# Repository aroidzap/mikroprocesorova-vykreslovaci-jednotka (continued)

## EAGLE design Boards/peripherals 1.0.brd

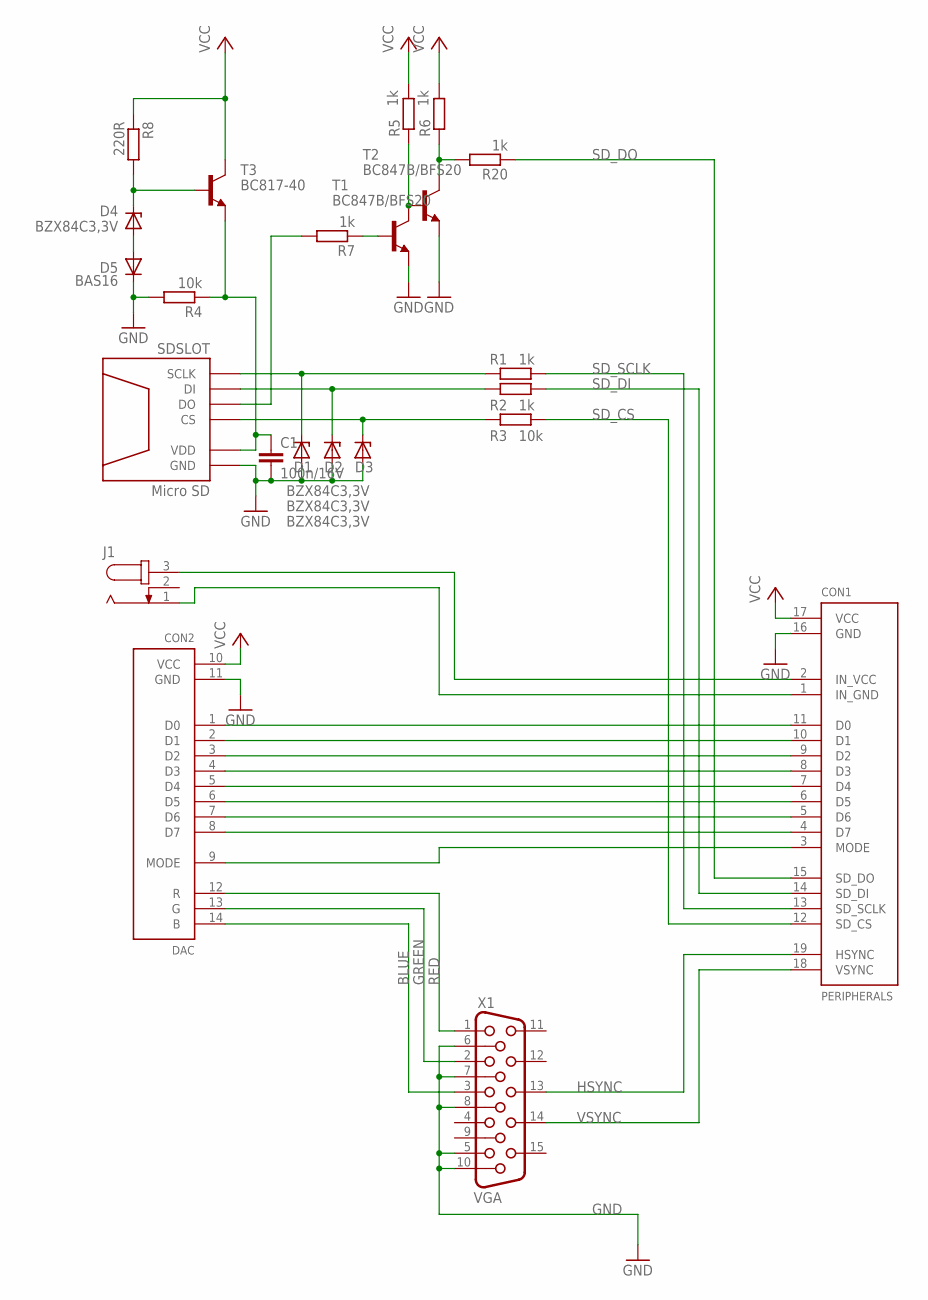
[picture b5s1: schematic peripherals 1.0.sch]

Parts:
C1: 100n/16V; C0603
CON1: PERIPHERALS; PERIPHERALS_CON
CON2: DAC; DAC_CON
D1, D2, D3, D4: BZX84C3,3V; SOT23
D5: BAS16; SOT23
J1: JACK-PLUG1; SPC4078
R1, R2, R5, R6, R7, R20: 1k; 0204/7
R3, R4: 10k; 0204/7
R8: 220R; R0603
SDSLOT: Micro SD; MICRO_SD_ATTEND
T1, T2: BC847B/BFS20; SOT23-BEC
T3: BC817-40; SOT23-BEC
X1: VGA; HDF15H

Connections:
BLUE: CON2.14 (B), X1.3
GND: C1.2, CON1.16 (GND), CON2.11 (GND), D1.1 (A), D2.1 (A), D3.1 (A), D5.3 (C), R4.2, SDSLOT.6 (GND), SDSLOT.CASE1 (GND), SDSLOT.CASE2 (GND), SDSLOT.CASE3 (GND), SDSLOT.CASE4 (GND), T1.E, T2.E, X1.5, X1.6, X1.7, X1.8, X1.10
GREEN: CON2.13 (G), X1.2
HSYNC: CON1.19 (HSYNC), X1.13
IN_GND: CON1.1 (IN_GND), J1.1
IN_VCC: CON1.2 (IN_VCC), J1.3
unnamed: D1.3 (C), R1.1, SDSLOT.5 (SCLK)
unnamed: D2.3 (C), R2.1, SDSLOT.3 (DI)
unnamed: D3.3 (C), R3.1, SDSLOT.2 (CS)
unnamed: D4.1 (A), D5.1 (A)
unnamed: C1.1, R4.1, SDSLOT.4 (VDD), T3.E
unnamed: D4.3 (C), R8.2, T3.B
unnamed: R6.1, R20.2, T2.C
unnamed: R7.2, SDSLOT.7 (DO)
unnamed: R5.1, T1.C, T2.B
unnamed: R7.1, T1.B
unnamed: CON1.11 (D0), CON2.1 (D0)
unnamed: CON1.10 (D1), CON2.2 (D1)
unnamed: CON1.9 (D2), CON2.3 (D2)
unnamed: CON1.8 (D3), CON2.4 (D3)
unnamed: CON1.7 (D4), CON2.5 (D4)
unnamed: CON1.6 (D5), CON2.6 (D5)
unnamed: CON1.5 (D6), CON2.7 (D6)
unnamed: CON1.4 (D7), CON2.8 (D7)
unnamed: CON1.3 (MODE), CON2.9 (MODE)
RED: CON2.12 (R), X1.1
SD_CS: CON1.12 (SD_CS), R3.2
SD_DI: CON1.14 (SD_DI), R2.2
SD_DO: CON1.15 (SD_DO), R20.1
SD_SCLK: CON1.13 (SD_SCLK), R1.2
VCC: CON1.17 (VCC), CON2.10 (VCC), R5.2, R6.2, R8.1, T3.C
VSYNC: CON1.18 (VSYNC), X1.14

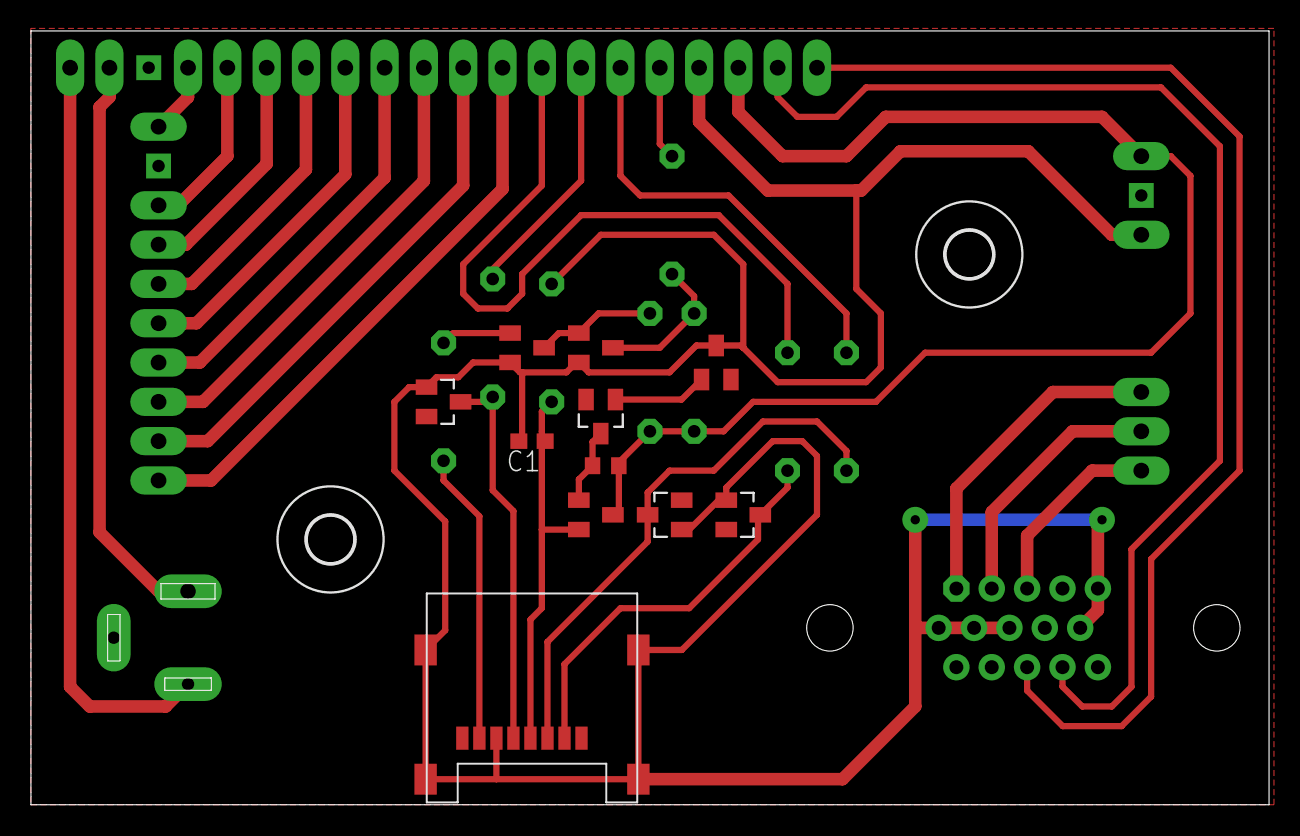
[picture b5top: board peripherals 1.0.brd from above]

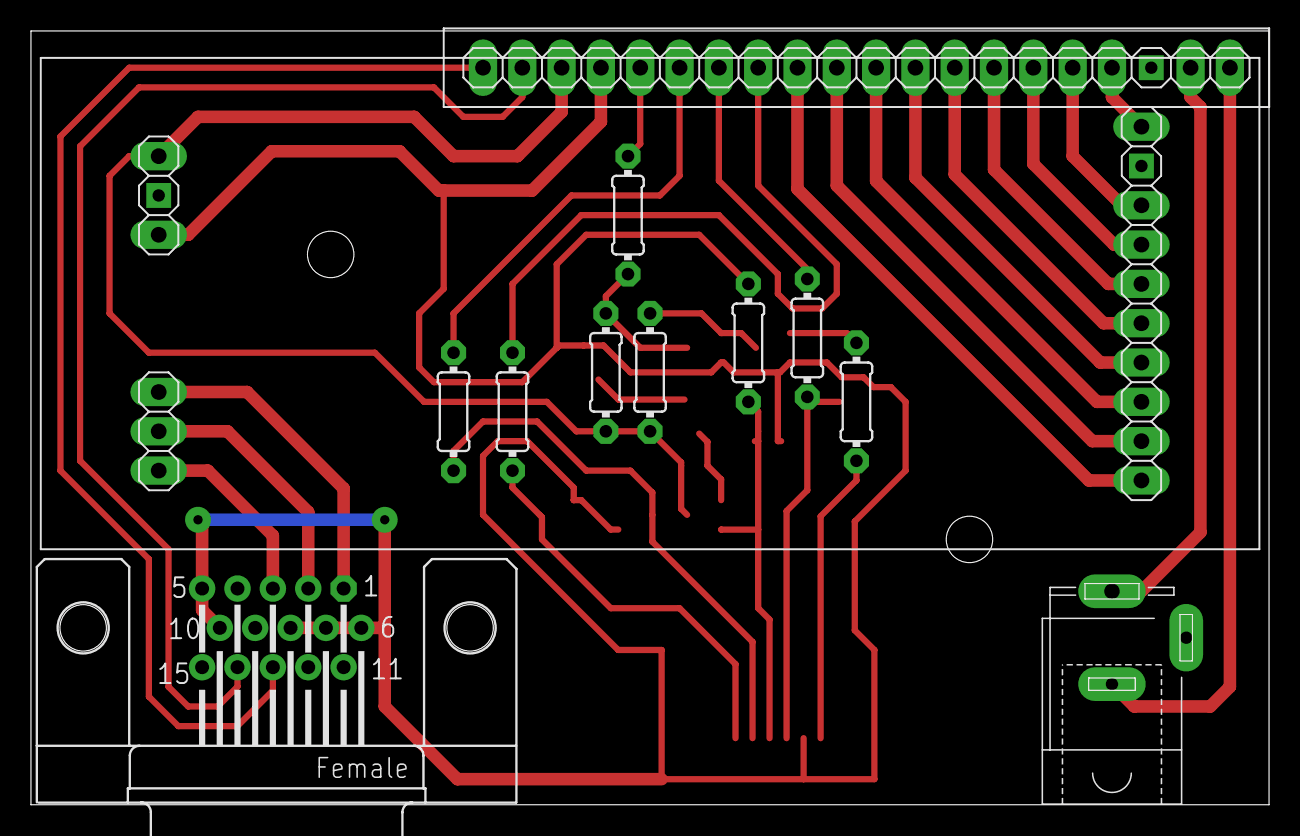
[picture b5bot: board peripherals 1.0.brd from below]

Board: 2 copper layers, 80.0 x 50.0 mm, 25 parts (12 on the bottom side), 32 nets.

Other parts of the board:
U$1, U$2: 3,0

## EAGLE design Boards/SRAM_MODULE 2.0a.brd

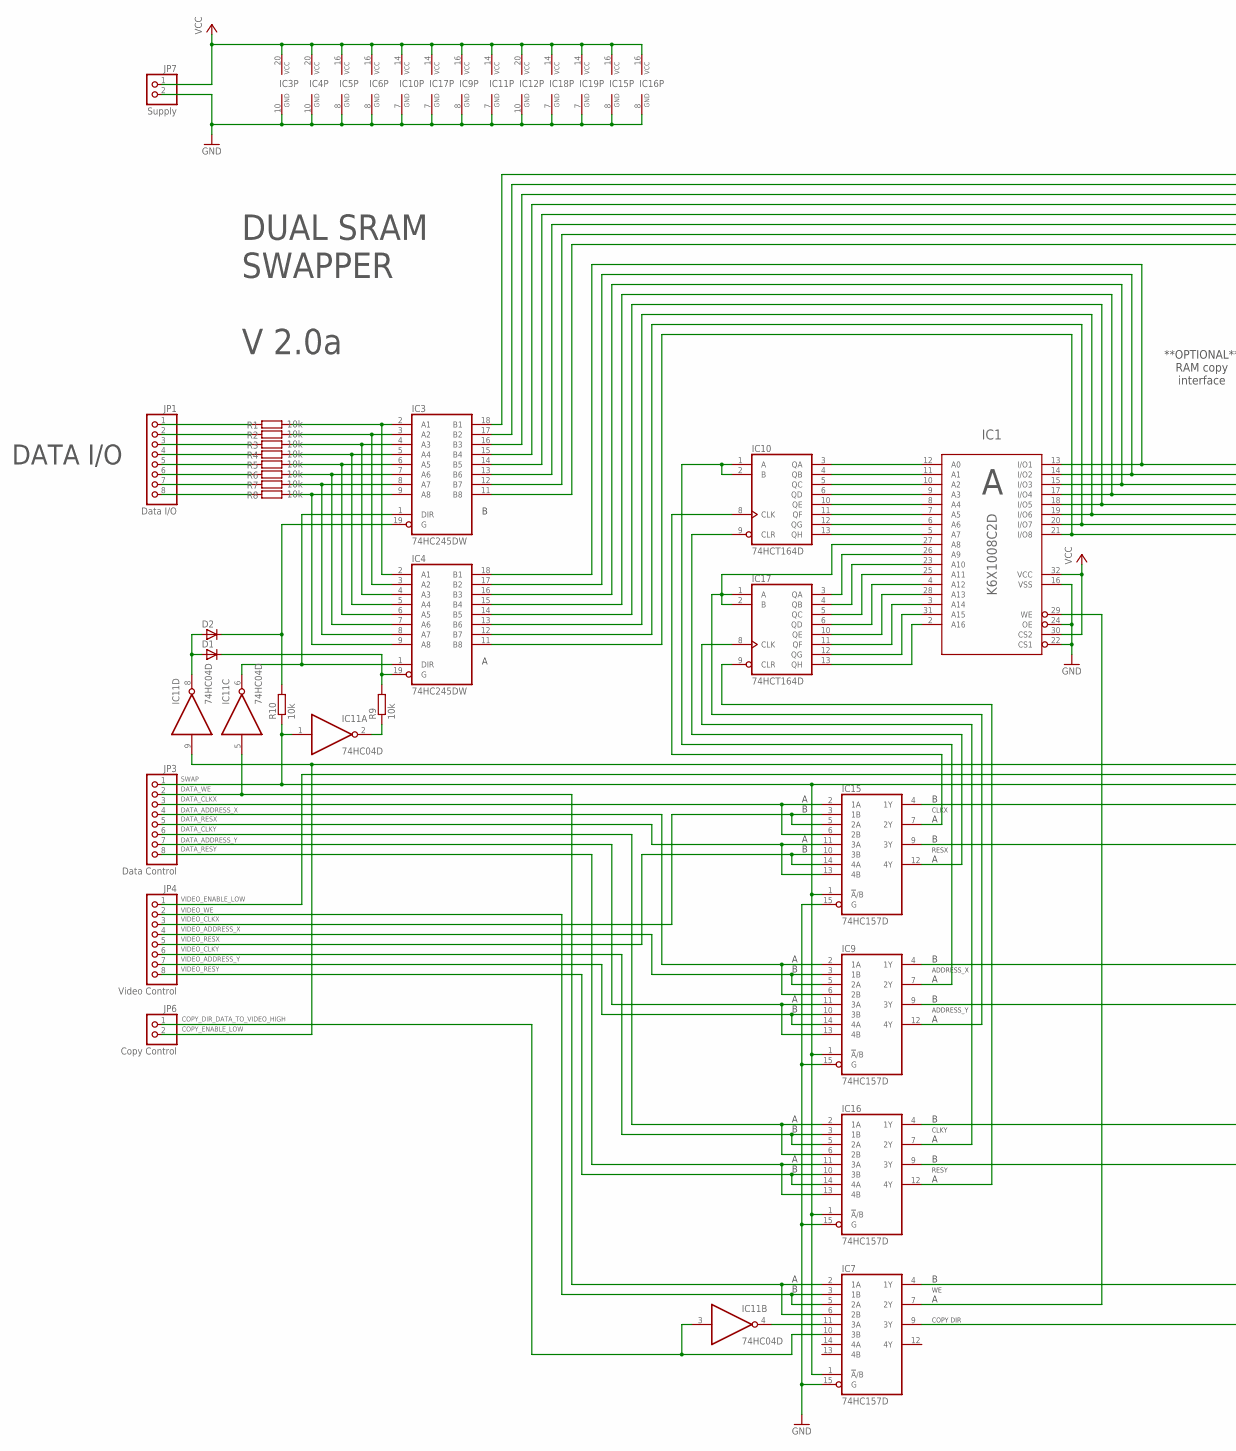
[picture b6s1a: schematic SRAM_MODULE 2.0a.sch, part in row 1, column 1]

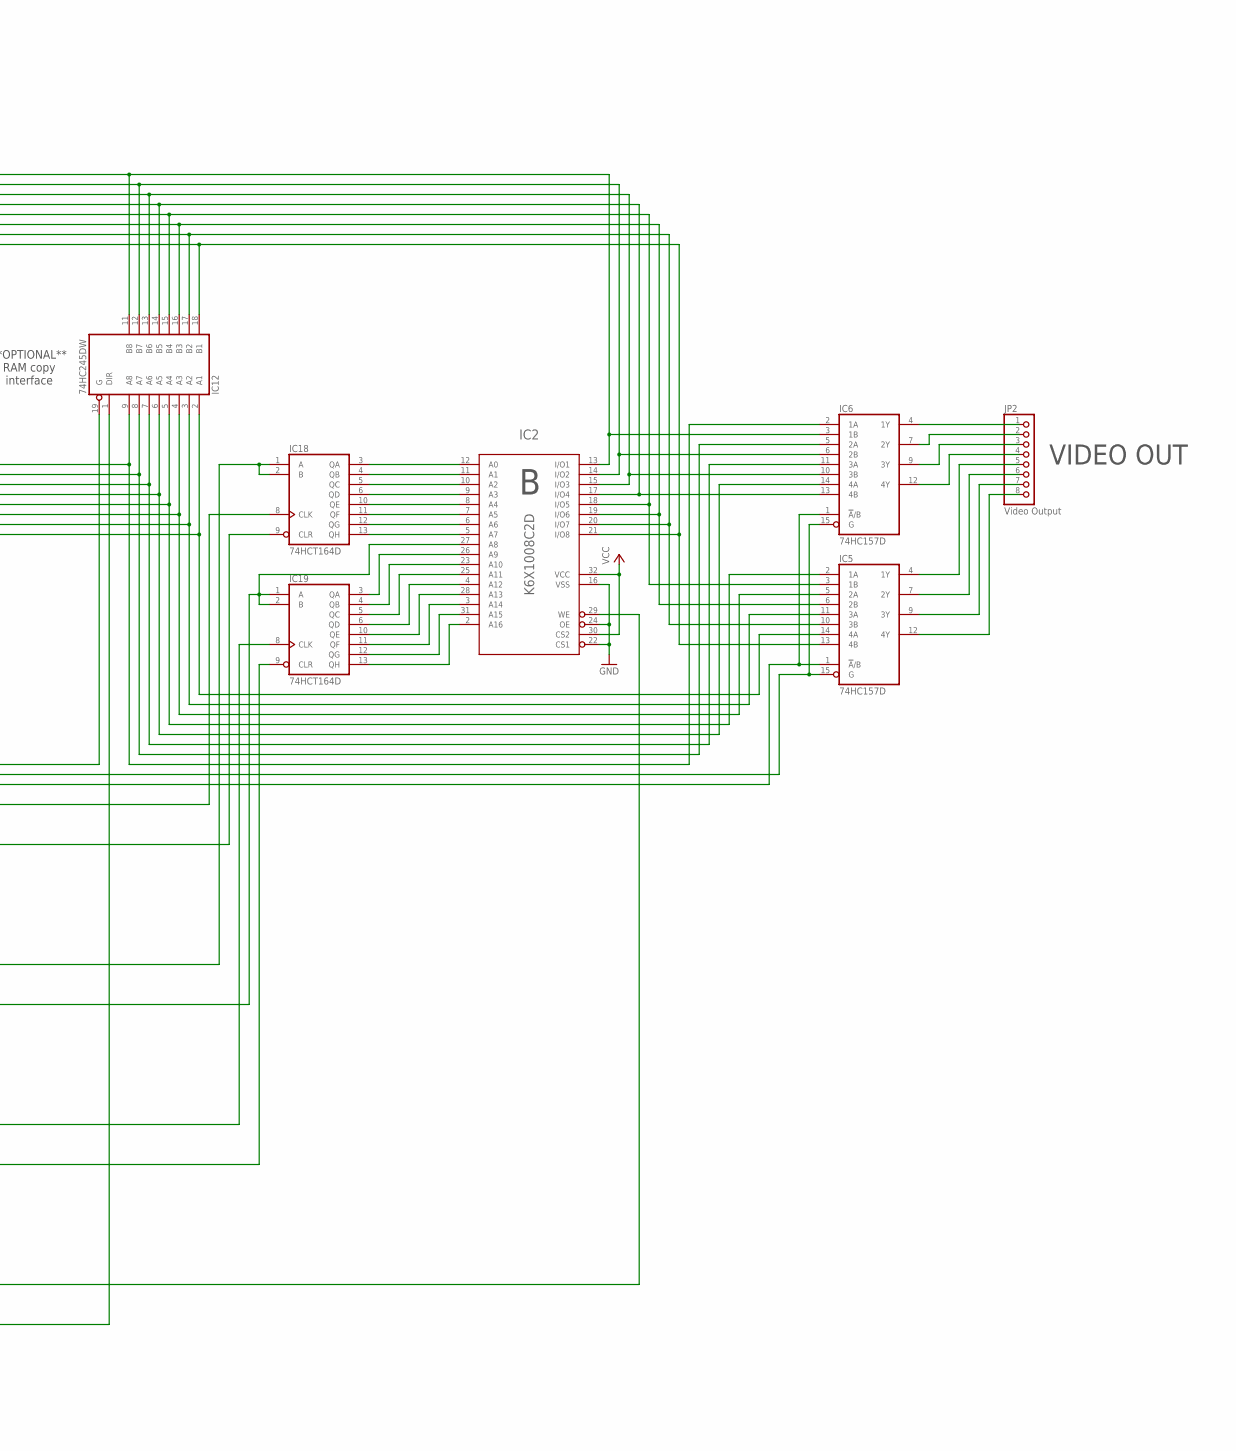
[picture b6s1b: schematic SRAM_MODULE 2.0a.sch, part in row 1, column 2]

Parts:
D1, D2: D-A1-C3; SOT23
IC1, IC2: K6X1008C2D; SOP32-5
IC3, IC4, IC12: 74HC245DW; SO20W
IC5, IC6, IC7, IC9, IC15, IC16: 74HC157D; SO16
IC10, IC17, IC18, IC19: 74HCT164D; SO14
IC11: 74HC04D; SO14
JP1: Data I/O; 1X08
JP2: Video Output; 1X08
JP3: Data Control; 1X08
JP4: Video Control; 1X08
JP6: Copy Control; 1X02
JP7: Supply; 1X02
R1, R2, R3, R4, R5, R6, R7, R8, R9, R10: 10k; R0603

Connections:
A_ADDRESS_X: IC9.7 (2Y), IC10.1 (A), IC10.2 (B)
A_ADDRESS_Y: IC1.27 (A8), IC9.12 (4Y), IC17.1 (A), IC17.2 (B)
A_CLKX: IC10.8 (CLK), IC15.7 (2Y)
A_CLKY: IC16.7 (2Y), IC17.8 (CLK)
A_I/O1: IC1.13 (I/O1), IC4.18 (B1), IC6.2 (1A), IC12.9 (A8)
A_I/O2: IC1.14 (I/O2), IC4.17 (B2), IC6.5 (2A), IC12.8 (A7)
A_I/O3: IC1.15 (I/O3), IC4.16 (B3), IC6.11 (3A), IC12.7 (A6)
A_I/O4: IC1.17 (I/O4), IC4.15 (B4), IC6.14 (4A), IC12.6 (A5)
A_I/O5: IC1.18 (I/O5), IC4.14 (B5), IC5.2 (1A), IC12.5 (A4)
A_I/O6: IC1.19 (I/O6), IC4.13 (B6), IC5.5 (2A), IC12.4 (A3)
A_I/O7: IC1.20 (I/O7), IC4.12 (B7), IC5.11 (3A), IC12.3 (A2)
A_I/O8: IC1.21 (I/O8), IC4.11 (B8), IC5.14 (4A), IC12.2 (A1)
A_RESX: IC10.9 (CLR), IC15.12 (4Y)
A_RESY: IC16.12 (4Y), IC17.9 (CLR)
A_WE: IC1.29 (WE), IC7.7 (2Y)
B_ADDRESS_X: IC9.4 (1Y), IC18.1 (A), IC18.2 (B)
B_ADDRESS_Y: IC2.27 (A8), IC9.9 (3Y), IC19.1 (A), IC19.2 (B)
B_CLKX: IC15.4 (1Y), IC18.8 (CLK)
B_CLKY: IC16.4 (1Y), IC19.8 (CLK)
B_I/O1: IC2.13 (I/O1), IC3.18 (B1), IC6.3 (1B), IC12.11 (B8)
B_I/O2: IC2.14 (I/O2), IC3.17 (B2), IC6.6 (2B), IC12.12 (B7)
B_I/O3: IC2.15 (I/O3), IC3.16 (B3), IC6.10 (3B), IC12.13 (B6)
B_I/O4: IC2.17 (I/O4), IC3.15 (B4), IC6.13 (4B), IC12.14 (B5)
B_I/O5: IC2.18 (I/O5), IC3.14 (B5), IC5.3 (1B), IC12.15 (B4)
B_I/O6: IC2.19 (I/O6), IC3.13 (B6), IC5.6 (2B), IC12.16 (B3)
B_I/O7: IC2.20 (I/O7), IC3.12 (B7), IC5.10 (3B), IC12.17 (B2)
B_I/O8: IC2.21 (I/O8), IC3.11 (B8), IC5.13 (4B), IC12.18 (B1)
B_RESX: IC15.9 (3Y), IC18.9 (CLR)
B_RESY: IC16.9 (3Y), IC19.9 (CLR)
B_WE: IC2.29 (WE), IC7.4 (1Y)
COPY_DIR_DATA_TO_VIDEO_HIGH: IC7.10 (3B), IC11.3 (I), JP6.1
COPY_ENABLE_LOW: IC11.9 (I), IC12.19 (G), JP6.2
DATA_ADDRESS_X: IC9.2 (1A), IC9.6 (2B), JP3.4
DATA_ADDRESS_Y: IC9.11 (3A), IC9.13 (4B), JP3.7
DATA_CLKX: IC15.2 (1A), IC15.6 (2B), JP3.3
DATA_CLKY: IC16.2 (1A), IC16.6 (2B), JP3.6
DATA_RESX: IC15.11 (3A), IC15.13 (4B), JP3.5
DATA_RESY: IC16.11 (3A), IC16.13 (4B), JP3.8
DATA_WE: IC7.2 (1A), IC7.6 (2B), IC11.5 (I), JP3.2
GND: IC1.16 (VSS), IC1.22 (CS1), IC1.24 (OE), IC2.16 (VSS), IC2.22 (CS1), IC2.24 (OE), IC3.10 (GND), IC4.10 (GND), IC5.8 (GND), IC6.8 (GND), IC7.8 (GND), IC7.15 (G), IC9.8 (GND), IC9.15 (G), IC10.7 (GND), IC11.7 (GND), IC12.10 (GND), IC15.8 (GND), IC15.15 (G), IC16.8 (GND), IC16.15 (G), IC17.7 (GND), IC18.7 (GND), IC19.7 (GND), JP7.2
INTERNAL_COPY_DIRECTION: IC7.9 (3Y), IC12.1 (DIR)
IO1: IC3.2 (A1), IC4.2 (A1), R1.2
IO2: IC3.3 (A2), IC4.3 (A2), R2.2
IO3: IC3.4 (A3), IC4.4 (A3), R3.2
IO4: IC3.5 (A4), IC4.5 (A4), R4.2
IO5: IC3.6 (A5), IC4.6 (A5), R5.2
IO6: IC3.7 (A6), IC4.7 (A6), R6.2
IO7: IC3.8 (A7), IC4.8 (A7), R7.2
IO8: IC3.9 (A8), IC4.9 (A8), R8.2
unnamed: IC1.12 (A0), IC10.3 (QA)
unnamed: IC7.11 (3A), IC11.4 (O)
unnamed: D2.3 (C), IC3.19 (G), R10.2
unnamed: D1.3 (C), IC4.19 (G), R9.2
unnamed: IC1.11 (A1), IC10.4 (QB)
unnamed: IC1.28 (A13), IC17.10 (QE)
unnamed: IC1.10 (A2), IC10.5 (QC)
unnamed: IC1.9 (A3), IC10.6 (QD)
unnamed: IC1.8 (A4), IC10.10 (QE)
unnamed: D1.1 (A), D2.1 (A), IC11.8 (O)
unnamed: IC1.7 (A5), IC10.11 (QF)
unnamed: IC1.6 (A6), IC10.12 (QG)
unnamed: JP1.8, R8.1
unnamed: JP1.7, R7.1
unnamed: JP1.6, R6.1
unnamed: JP1.5, R5.1
unnamed: IC1.5 (A7), IC10.13 (QH)
unnamed: JP1.4, R4.1
unnamed: IC1.26 (A9), IC17.3 (QA)
unnamed: IC1.23 (A10), IC17.4 (QB)
unnamed: IC1.25 (A11), IC17.5 (QC)
unnamed: IC1.4 (A12), IC17.6 (QD)
unnamed: IC1.3 (A14), IC17.11 (QF)
unnamed: IC1.31 (A15), IC17.12 (QG)
unnamed: IC1.2 (A16), IC17.13 (QH)
unnamed: JP1.3, R3.1
unnamed: IC2.26 (A9), IC19.3 (QA)
unnamed: IC2.23 (A10), IC19.4 (QB)
unnamed: IC2.25 (A11), IC19.5 (QC)
unnamed: IC2.4 (A12), IC19.6 (QD)
unnamed: IC2.28 (A13), IC19.10 (QE)
unnamed: IC2.3 (A14), IC19.11 (QF)
unnamed: IC2.31 (A15), IC19.12 (QG)
unnamed: IC2.2 (A16), IC19.13 (QH)
unnamed: IC2.12 (A0), IC18.3 (QA)
unnamed: IC2.11 (A1), IC18.4 (QB)
unnamed: IC2.10 (A2), IC18.5 (QC)
unnamed: IC2.9 (A3), IC18.6 (QD)
unnamed: IC2.8 (A4), IC18.10 (QE)
unnamed: JP1.2, R2.1
unnamed: IC2.7 (A5), IC18.11 (QF)
unnamed: IC2.6 (A6), IC18.12 (QG)
unnamed: IC3.1 (DIR), IC4.1 (DIR), IC11.6 (O)
unnamed: IC2.5 (A7), IC18.13 (QH)
unnamed: IC11.2 (O), R9.1
unnamed: JP1.1, R1.1
O1: IC6.4 (1Y), JP2.1
O2: IC6.7 (2Y), JP2.2
O3: IC6.9 (3Y), JP2.3
O4: IC6.12 (4Y), JP2.4
O5: IC5.4 (1Y), JP2.5
O6: IC5.7 (2Y), JP2.6
O7: IC5.9 (3Y), JP2.7
O8: IC5.12 (4Y), JP2.8
SWAP: IC5.1 (!A!/B), IC6.1 (!A!/B), IC7.1 (!A!/B), IC9.1 (!A!/B), IC11.1 (I), IC15.1 (!A!/B), IC16.1 (!A!/B), JP3.1, R10.1
VCC: IC1.30 (CS2), IC1.32 (VCC), IC2.30 (CS2), IC2.32 (VCC), IC3.20 (VCC), IC4.20 (VCC), IC5.16 (VCC), IC6.16 (VCC), IC7.16 (VCC), IC9.16 (VCC), IC10.14 (VCC), IC11.14 (VCC), IC12.20 (VCC), IC15.16 (VCC), IC16.16 (VCC), IC17.14 (VCC), IC18.14 (VCC), IC19.14 (VCC), JP7.1
VIDEO_ADDRESS_X: IC9.3 (1B), IC9.5 (2A), JP4.4
VIDEO_ADDRESS_Y: IC9.10 (3B), IC9.14 (4A), JP4.7
VIDEO_CLKX: IC15.3 (1B), IC15.5 (2A), JP4.3
VIDEO_CLKY: IC16.3 (1B), IC16.5 (2A), JP4.6
VIDEO_ENABLE_LOW: IC5.15 (G), IC6.15 (G), JP4.1
VIDEO_RESX: IC15.10 (3B), IC15.14 (4A), JP4.5
VIDEO_RESY: IC16.10 (3B), IC16.14 (4A), JP4.8
VIDEO_WE: IC7.3 (1B), IC7.5 (2A), JP4.2

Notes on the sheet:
DATA I/O
VIDEO OUT
**OPTIONAL** RAM copy interface
CLKX
ADDRESS_X
RESX
CLKY
ADDRESS_Y
RESY
COPY DIR
DUAL SRAM SWAPPER V 2.0a

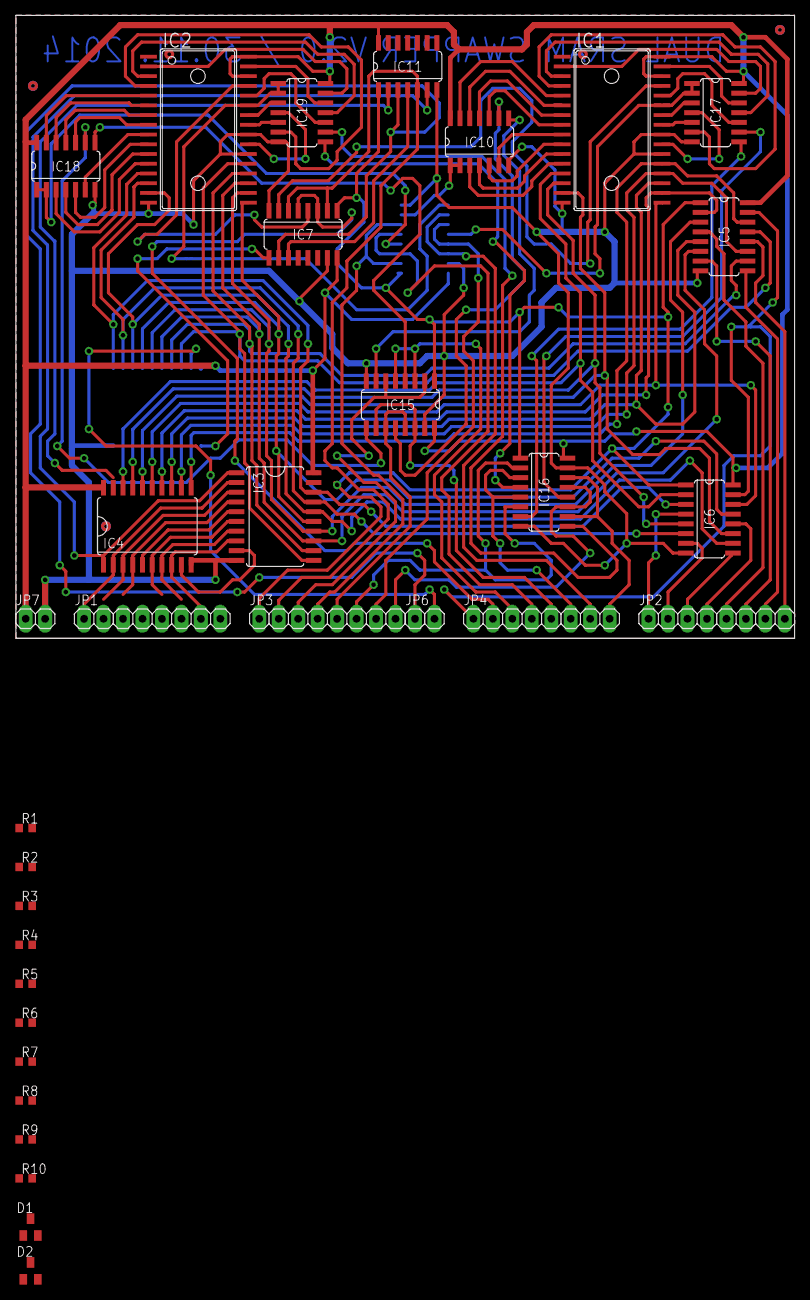
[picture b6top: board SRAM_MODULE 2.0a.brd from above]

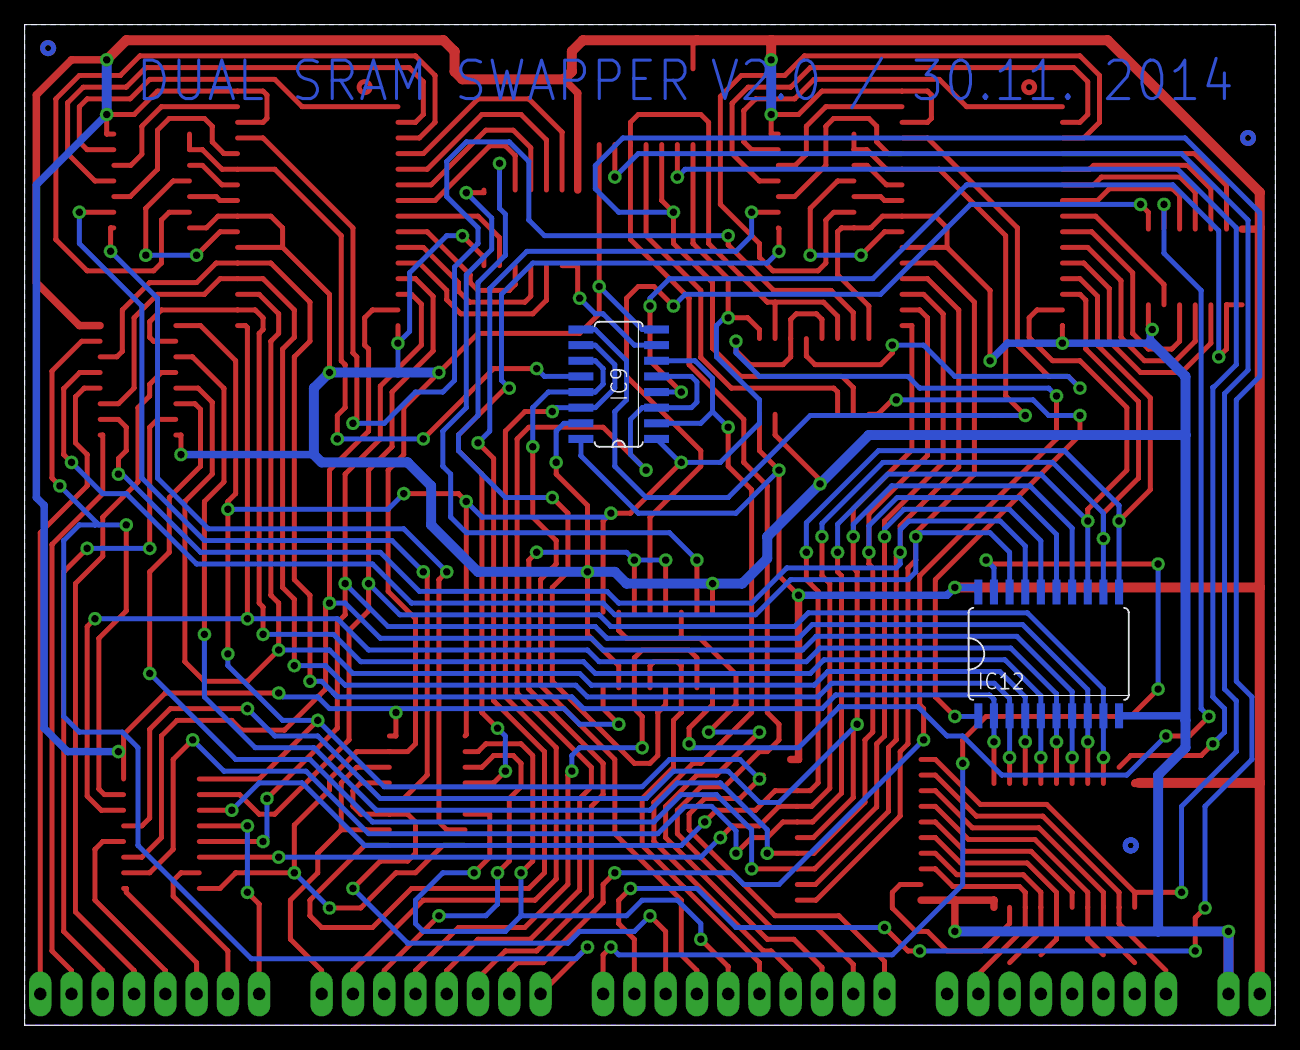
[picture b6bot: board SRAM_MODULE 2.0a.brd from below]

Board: 2 copper layers, 101.6 x 81.3 mm, 34 parts (2 on the bottom side), 113 nets.

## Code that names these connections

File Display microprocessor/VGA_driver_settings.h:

/*
*	Copyright (c) 2015 Tomá Pazdiora
*	See the file "LICENSE.txt" for the full license governing this code.
*/

#define VGADDR DDRD
#define VGAPORT PORTD
#define VGAPIN PIND

#define RXD 0 //swap_request
#define TXD 1

#define VIDEO_ENABLE 3
#define HSYNC 4
#define VSYNC 5

#define COPY_DIR 6

#define VGADDR2 DDRB
#define VGAPORT2 PORTB
#define VGAPIN2 PINB

#define ADR_Y	0
#define CLK_Y	1
#define RES_X	2
#define ADR_X	3
#define CLK_X	4

#define COPY_WRITE_ENABLE 5

#define COPY_HIGH	6

#define SWAP_OUT	7

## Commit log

2015-04-06 Added licensing information
2015-04-06 edited .gitignore
2015-04-06 removed .atsuo file
2015-04-07 edited variable type
2015-04-07 repaired mix function
2015-04-07 variable name correction
2015-04-07 fixup! variable name correction
2015-04-09 Added information about fuses
2015-04-11 added documentations
2015-04-11 Updated README.txt file
2015-04-12 added pdf versions of schematics
2015-04-12 edited SD_init_basic()
2015-04-12 added info about viewing boards
2015-04-12 added Czech translations of README files
2015-04-12 updated README files
